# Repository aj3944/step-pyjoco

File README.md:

# OpenSCAD Humanoid with MuJoCo Controls

## Description

This repository contains the design and control code for an open-source humanoid robot. The design of the robot is created using OpenSCAD, a script-based 3D CAD modeler, allowing for parametric and fully customizable design files. The control of the humanoid is managed using Python, interfacing with the MuJoCo (Multi-Joint dynamics with Contact) physics engine, which provides a realistic simulation environment for the robot.

## Features
- **Parametric Design**: The humanoid robot's structure is fully defined in OpenSCAD, enabling users to modify dimensions, joint angles, and other physical properties easily.
- **Python Control Scripts**: Control algorithms written in Python, allowing users to simulate, test, and refine control strategies for the humanoid's movements.
- **MuJoCo Integration**: The repository leverages MuJoCo's advanced physics simulation capabilities to create a realistic environment for testing the robot's dynamics and control systems.
- **Customizable Components**: Users can design and simulate various components, such as arms, legs, and sensors, to suit different research and development needs.
- **Simulation Environment**: Pre-built environments in MuJoCo for testing walking, balancing, and complex maneuvers.

## Getting Started
1. **Clone the Repository**: Start by cloning the repository to your local machine.
2. **OpenSCAD Design**: Customize the humanoid design using the provided OpenSCAD files.
3. **Python & MuJoCo Setup**: Follow the setup instructions to install Python dependencies and configure MuJoCo for your system.
4. **Run Simulations**: Use the provided Python scripts to simulate the humanoid's behavior in MuJoCo, with various control strategies available.

## Prerequisites
- OpenSCAD installed for editing and viewing the 3D models.
- Python 3.x with necessary libraries (e.g., NumPy, MuJoCo Python bindings).
- MuJoCo installed and properly configured with a valid license.

## Usage
- **Customization**: Modify the `step_bot.scad` file to change the humanoid's design parameters.
- **Control Algorithms**: Implement and test control algorithms in Python using the provided templates.
- **Simulation**: Run the simulation scripts to observe the robot's performance under different conditions.

## Contributing
Contributions are welcome! Feel free to fork the repository, make your changes, and submit a pull request. Please make sure to document any new features or modifications.

## License
This project is licensed under the MIT License - see the LICENSE file for details.

## Contact
For any questions, suggestions, or contributions, please reach out to aj3944@nyu.edu.

---

This repository bridges the gap between mechanical design and control systems, enabling researchers, educators, and enthusiasts to explore humanoid robotics in an open-source and customizable environment.

# Stair Traversal and Exploration Project (STEP)

**Team STEP** at NYU is dedicated to advancing the capabilities of autonomous robots in navigating complex, stair-filled environments. The project focuses on designing and prototyping robotic systems with specialized hardware and control algorithms that enable precise movement on uneven and inclined surfaces. Leveraging sensor fusion techniques, STEP integrates LIDAR, IMUs, and vision systems to enhance real-time environmental perception and decision-making. The ultimate goal is to create robots capable of autonomous exploration and traversal in challenging terrains, with applications in search and rescue, urban exploration, and infrastructure inspection.

As part of NYU's Vertically Integrated Projects (VIP) program, STEP offers students the chance to earn academic credit while contributing to cutting-edge research. Participants from various disciplines collaborate on long-term, multidisciplinary tasks, developing skills in robotics, control systems, and sensor integration. This project not only provides hands-on experience but also positions students to make impactful contributions to the field of autonomous robotics.

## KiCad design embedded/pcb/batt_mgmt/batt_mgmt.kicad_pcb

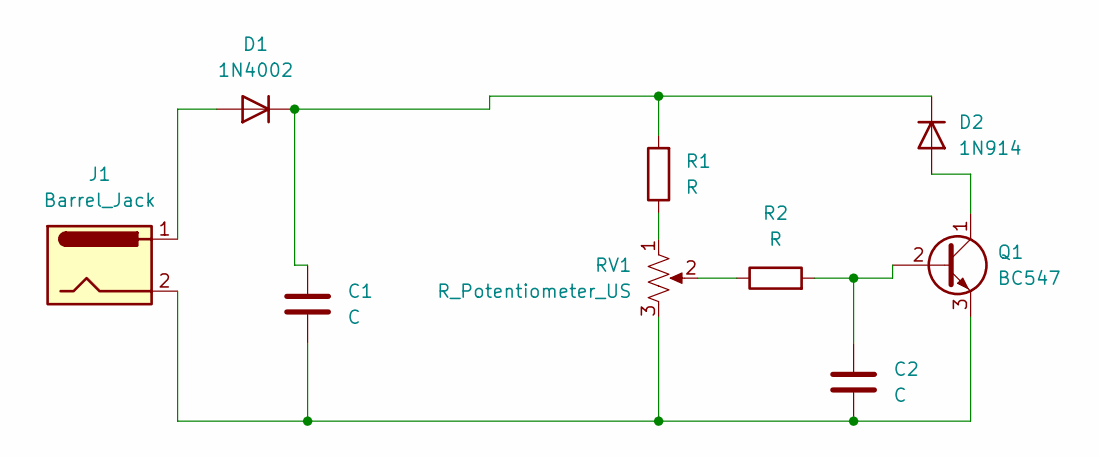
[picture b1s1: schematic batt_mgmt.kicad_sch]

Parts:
C1, C2: C
D1: 1N4002; D_DO-41_SOD81_P10.16mm_Horizontal
D2: 1N914; D_DO-35_SOD27_P7.62mm_Horizontal
J1: Barrel_Jack
Q1: BC547; TO-92_Inline
R1, R2: R
RV1: R_Potentiometer_US

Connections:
unnamed: D1.2 (A), J1.1
unnamed: C1.1, D1.1 (K), D2.1 (K), R1.2
unnamed: D2.2 (A), Q1.1 (C)
unnamed: C2.1, Q1.2 (B), R2.2
unnamed: C1.2, C2.2, J1.2, Q1.3 (E), RV1.3
unnamed: R1.1, RV1.1
unnamed: R2.1, RV1.2

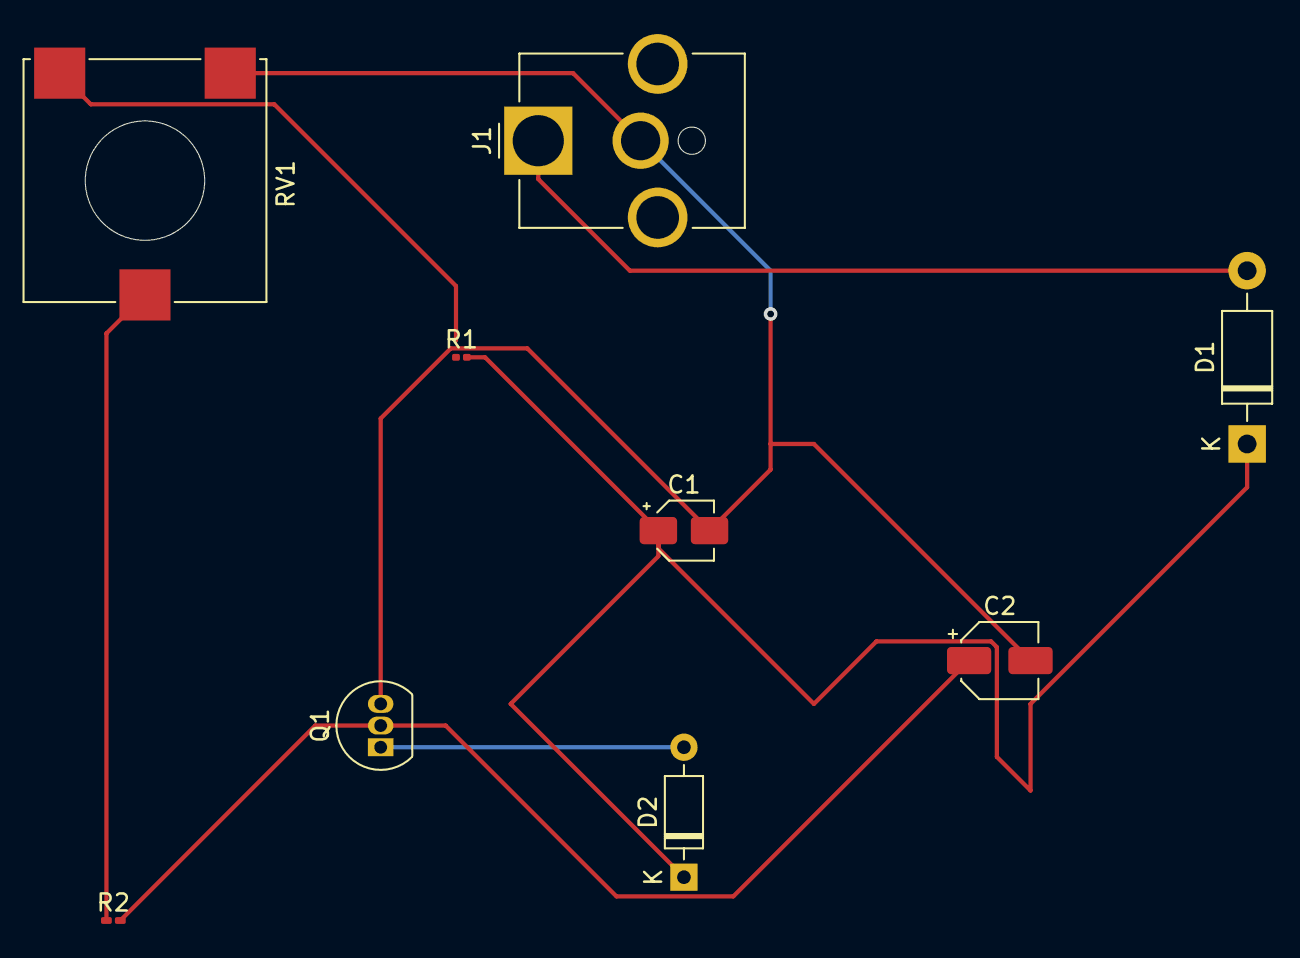
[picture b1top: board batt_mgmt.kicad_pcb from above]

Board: 2 copper layers, 9 parts (0 on the bottom side), 7 nets.

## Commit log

2024-09-02 STEP6 Assets
2024-09-02 added 3d_printable openSCAD files
2024-09-02 added README.md
2024-09-02 added STEP logo
2024-09-02 midwalk
2024-09-05 reset
2024-09-09 step test
2024-09-11 pre rl
2024-09-21 cleaned unused variables
2024-09-21 added gitignore
2024-09-26 pcb training
2024-09-26 updated git ignore for embed python
2024-09-27 embedded code added
2024-09-30 encoder read
2024-09-30 encoder parse
2024-10-02 partial completion of commands from data sheet
2024-10-02 updated motor file
2024-10-05 book + new commands
2024-10-05 added extra commands and labels
2024-10-05 embedded requirements.txt
2024-10-05 move global testing
2024-10-05 update move global testing
2024-10-05 updated motor.py to have torque and phase current reading and added partial detection of touch
2024-10-13 BAD PID
2024-10-13 T-compliance
2024-10-13 i to zero
2024-10-14 update to return to position
2024-10-14 better PID
2024-10-15 6 dof sim added
2024-11-08 new bot
2024-11-09 origins updates
2024-11-09 Create 6 DOF
2024-11-09 New 6 DOF
2024-11-12 w/o jetson
2024-11-12 sim fixed
2024-11-12 fixed scale using old meshes
2024-11-13 sim2real
2024-11-13 motor ID assignments
2024-11-13 find_motor_id code
2024-11-20 unibody/11/20/2024
2024-11-20 motor_move
2024-11-20 all motor limit testing
2024-11-29 new 3d printable thigh
    might have scaling issues
2024-11-29 new home position
    might have scaling issues
2024-11-29 for reference, will update the battery position
2025-02-04 new motor controls
2025-02-14 new motor commands
2025-02-14 new mode
2025-02-14 Green_Team_New_File
2025-02-16 Added commands 2.1, 2.3, 2.5
2025-02-18 Implemented command #
2025-02-18 added frame functions for 2.7, 2.9, and 2.11. added parse functions for 2.1, 2.7, and 2.11. fixed some typos
2025-02-20 Create blueteam.py
    Initial Dump
2025-02-20 updated with commands 21, 23, 31, 33, 35
2025-02-20 added 2.15 and 2.17, changed my old names to be more concise
2025-02-21 individually converted values to bytes on 2.3
2025-02-21 created wrappers fro 2.1 - 2.11 (odd)
2025-02-21 abs position and incremental position closed loop control
2025-02-21 motor2 commands for 2.25
2025-02-21 tested all commands
2025-03-13 map_outputs_to_torque
2025-03-21 Added files for testing neural network
2025-04-14 bot code
2025-04-15 updated multimotor commands
2025-12-04 small updates/new branch
